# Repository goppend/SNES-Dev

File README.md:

# SNES-Dev
Repo for my Super NES development projects

## SNES-Cart-Dbg
### SNES cartridge debugging probe. With lock-on technology!

## SNES-Cart-Holder
### PCB intermediary for plugging SNES cartridges into things.

## SNES-EEPROM
### Small board for adapting PLCC EEPROMs to SNES mask ROMs.

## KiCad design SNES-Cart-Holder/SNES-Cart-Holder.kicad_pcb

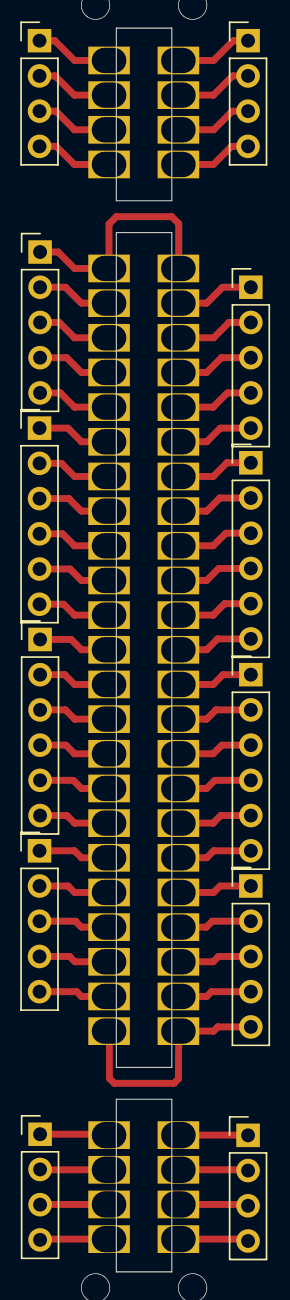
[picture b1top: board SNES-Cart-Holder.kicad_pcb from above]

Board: 2 copper layers, 13 parts (0 on the bottom side), 60 nets.

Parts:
J1, J6, J8, J13: Conn_01x04_Male; PinHeader_1x04_P2.54mm_Vertical
J2, J5, J9, J12: Conn_01x05_Male; PinHeader_1x05_P2.54mm_Vertical
J3, J4, J10, J11: Conn_01x06_Male; PinHeader_1x06_P2.54mm_Vertical
J7: Conn_02x31_Top_Bottom; SNES_Cart_Holder_Pogo

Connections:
/#CPURD: J5.2, J7.23
/#CPUWR: J7.54, J12.1
/#IRQ: J4.3, J7.18
/#PARD: J1.4, J7.4
/#PAWR: J7.35, J8.4
/#RAMSEL: J7.32, J8.1
/#RESET: J5.5, J7.26
/#ROMSEL: J7.49, J11.2
/+5V: J7.27, J7.58, J12.5
/CA0: J4.2, J7.17
/CA1: J4.1, J7.16
/CA2: J3.6, J7.15
/CA3: J3.5, J7.14
/CA4: J3.4, J7.13
/CA5: J3.3, J7.12
/CA6: J3.2, J7.11
/CA7: J3.1, J7.10
/CA8: J2.5, J7.9
/CA9: J2.4, J7.8
/CA10: J2.3, J7.7
/CA11: J2.2, J7.6
/CA12: J7.37, J9.1
/CA13: J7.38, J9.2
/CA14: J7.39, J9.3
/CA15: J7.40, J9.4
/CA16: J7.41, J9.5
/CA17: J7.42, J10.1
/CA18: J7.43, J10.2
/CA19: J7.44, J10.3
/CA20: J7.45, J10.4
/CA21: J7.46, J10.5
/CA22: J7.47, J10.6
/CA23: J7.48, J11.1
/CIC0: J5.3, J7.24
/CIC1: J7.55, J12.2
/CIC2: J5.4, J7.25
/CIC3: J7.56, J12.3
/D0: J4.4, J7.19
/D1: J4.5, J7.20
/D2: J4.6, J7.21
/D3: J5.1, J7.22
/D4: J7.50, J11.3
/D5: J7.51, J11.4
/D6: J7.52, J11.5
/D7: J7.53, J11.6
/EXPAND: J1.2, J7.2
/GND: J2.1, J7.5, J7.36
/MCK: J1.1, J7.1
/PA0: J6.1, J7.28
/PA1: J7.59, J13.1
/PA2: J6.2, J7.29
/PA3: J7.60, J13.2
/PA4: J6.3, J7.30
/PA5: J7.61, J13.3
/PA6: J1.3, J7.3
/PA7: J7.34, J8.3
/REFRESH: J7.33, J8.2
/SOUND_L: J6.4, J7.31
/SOUND_R: J7.62, J13.4
/SYSCK: J7.57, J12.4

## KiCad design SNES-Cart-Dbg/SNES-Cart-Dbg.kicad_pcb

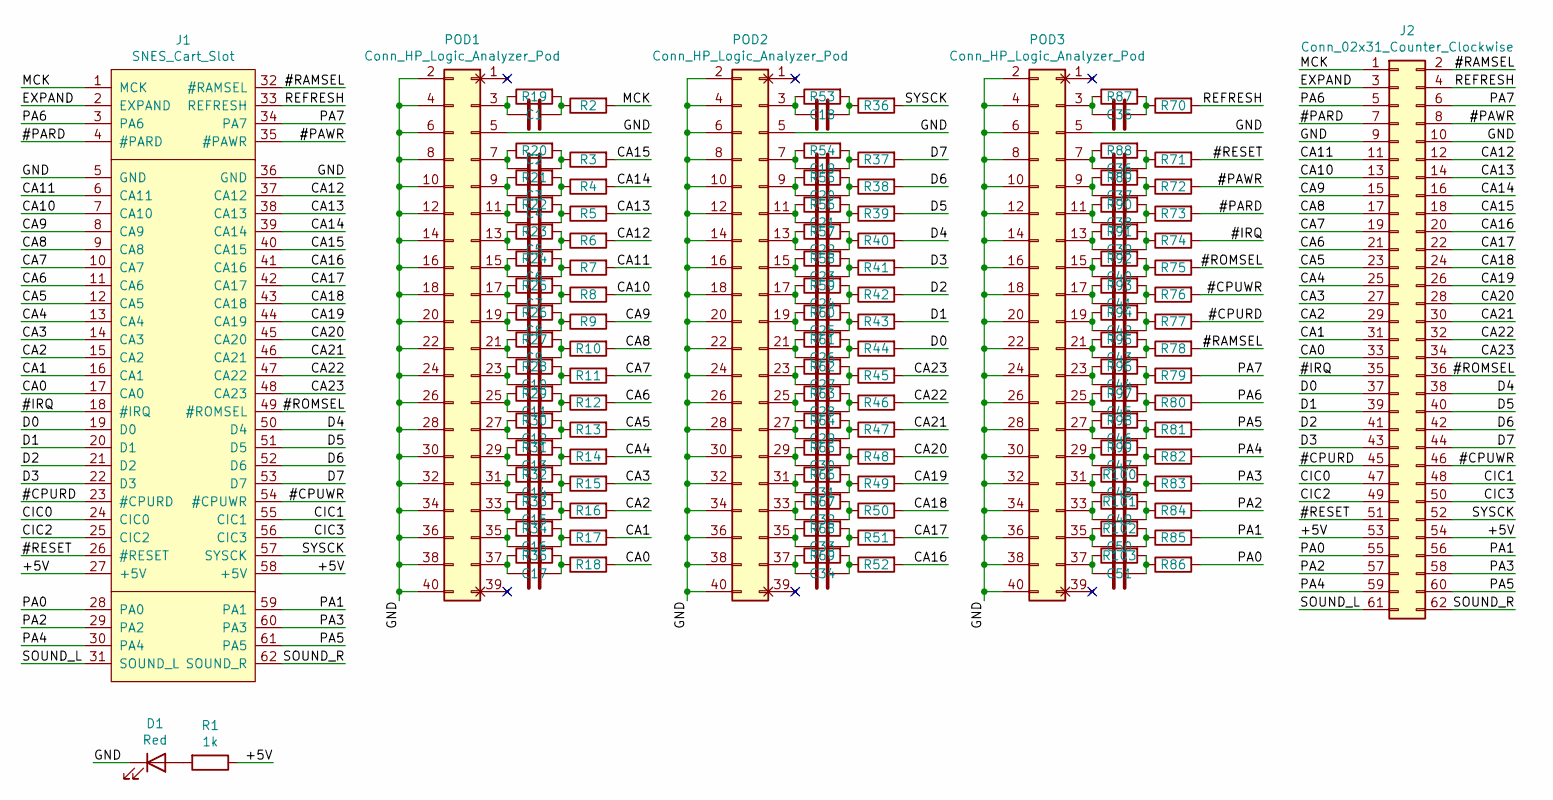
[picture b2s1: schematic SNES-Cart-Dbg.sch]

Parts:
C1: 8 pF; R_0805
C2, C3, C4, C5, C6, C7, C8, C9, C10, C11, C12, C13, C14, C15, C16, C17, C18, C19, C20, C21, C22, C23, C24, C25, C26, C27, C28, C29, C30, C31, C32, C33, C34, C35, C36, C37, C38, C39, C40, C41, C42, C43, C44, C45, C46, C47, C48, C49, C50, C51: C; R_0805
D1: Red; LED_D5.0mm
J1: SNES_Cart_Slot; SNES-Cart
J2: Conn_02x31_Counter_Clockwise; SNES_Connector_Right_Angle
POD1, POD2, POD3: Conn_HP_Logic_Analyzer_Pod; HP_Logic_Analyzer_Pod_Connector
R1: 1k; R_Axial_DIN0204_L3.6mm_D1.6mm_P7.62mm_Horizontal
R2: 250; R_0805
R3, R4, R5, R6, R7, R8, R9, R10, R11, R12, R13, R14, R15, R16, R17, R18, R20, R21, R22, R23, R24, R25, R26, R27, R28, R29, R30, R31, R32, R33, R34, R35, R36, R37, R38, R39, R40, R41, R42, R43, R44, R45, R46, R47, R48, R49, R50, R51, R52, R53, R54, R55, R56, R57, R58, R59, R60, R61, R62, R63, R64, R65, R66, R67, R68, R69, R70, R71, R72, R73, R74, R75, R76, R77, R78, R79, R80, R81, R82, R83, R84, R85, R86, R87, R88, R89, R90, R91, R92, R93, R94, R95, R96, R97, R98, R99, R100, R101, R102, R103: R; R_0805
R19: 10k; R_0805

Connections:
/#CPURD: J1.23 (#CPURD), J2.45, R77.2
/#CPUWR: J1.54 (#CPUWR), J2.46, R76.2
/#IRQ: J1.18 (#IRQ), J2.35, R74.2
/#PARD: J1.4 (#PARD), J2.7, R73.2
/#PAWR: J1.35 (#PAWR), J2.8, R72.2
/#RAMSEL: J1.32 (#RAMSEL), J2.2, R78.2
/#RESET: J1.26 (#RESET), J2.51, R71.2
/#ROMSEL: J1.49 (#ROMSEL), J2.36, R75.2
/+5V: J1.27 (+5V), J1.58 (+5V), J2.53, J2.54, R1.1
/CA0: J1.17 (CA0), J2.33, R18.2
/CA1: J1.16 (CA1), J2.31, R17.2
/CA2: J1.15 (CA2), J2.29, R16.2
/CA3: J1.14 (CA3), J2.27, R15.2
/CA4: J1.13 (CA4), J2.25, R14.2
/CA5: J1.12 (CA5), J2.23, R13.2
/CA6: J1.11 (CA6), J2.21, R12.2
/CA7: J1.10 (CA7), J2.19, R11.2
/CA8: J1.9 (CA8), J2.17, R10.2
/CA9: J1.8 (CA9), J2.15, R9.2
/CA10: J1.7 (CA10), J2.13, R8.2
/CA11: J1.6 (CA11), J2.11, R7.2
/CA12: J1.37 (CA12), J2.12, R6.2
/CA13: J1.38 (CA13), J2.14, R5.2
/CA14: J1.39 (CA14), J2.16, R4.2
/CA15: J1.40 (CA15), J2.18, R3.2
/CA16: J1.41 (CA16), J2.20, R52.2
/CA17: J1.42 (CA17), J2.22, R51.2
/CA18: J1.43 (CA18), J2.24, R50.2
/CA19: J1.44 (CA19), J2.26, R49.2
/CA20: J1.45 (CA20), J2.28, R48.2
/CA21: J1.46 (CA21), J2.30, R47.2
/CA22: J1.47 (CA22), J2.32, R46.2
/CA23: J1.48 (CA23), J2.34, R45.2
/CIC0: J1.24 (CIC0), J2.47
/CIC1: J1.55 (CIC1), J2.48
/CIC2: J1.25 (CIC2), J2.49
/CIC3: J1.56 (CIC3), J2.50
/D0: J1.19 (D0), J2.37, R44.2
/D1: J1.20 (D1), J2.39, R43.2
/D2: J1.21 (D2), J2.41, R42.2
/D3: J1.22 (D3), J2.43, R41.2
/D4: J1.50 (D4), J2.38, R40.2
/D5: J1.51 (D5), J2.40, R39.2
/D6: J1.52 (D6), J2.42, R38.2
/D7: J1.53 (D7), J2.44, R37.2
/EXPAND: J1.2 (EXPAND), J2.3
/GND: D1.1 (K), J1.5 (GND), J1.36 (GND), J2.9, J2.10, POD1.2 (Gnd), POD1.4 (Gnd), POD1.5 (Sig_Ref), POD1.6 (Gnd), POD1.8 (Gnd), POD1.10 (Gnd), POD1.12 (Gnd), POD1.14 (Gnd), POD1.16 (Gnd), POD1.18 (Gnd), POD1.20 (Gnd), POD1.22 (Gnd), POD1.24 (Gnd), POD1.26 (Gnd), POD1.28 (Gnd), POD1.30 (Gnd), POD1.32 (Gnd), POD1.34 (Gnd), POD1.36 (Gnd), POD1.38 (Gnd), POD1.40 (Gnd), POD2.2 (Gnd), POD2.4 (Gnd), POD2.5 (Sig_Ref), POD2.6 (Gnd), POD2.8 (Gnd), POD2.10 (Gnd), POD2.12 (Gnd), POD2.14 (Gnd), POD2.16 (Gnd), POD2.18 (Gnd), POD2.20 (Gnd), POD2.22 (Gnd), POD2.24 (Gnd), POD2.26 (Gnd), POD2.28 (Gnd), POD2.30 (Gnd), POD2.32 (Gnd), POD2.34 (Gnd), POD2.36 (Gnd), POD2.38 (Gnd), POD2.40 (Gnd), POD3.2 (Gnd), POD3.4 (Gnd), POD3.5 (Sig_Ref), POD3.6 (Gnd), POD3.8 (Gnd), POD3.10 (Gnd), POD3.12 (Gnd), POD3.14 (Gnd), POD3.16 (Gnd), POD3.18 (Gnd), POD3.20 (Gnd), POD3.22 (Gnd), POD3.24 (Gnd), POD3.26 (Gnd), POD3.28 (Gnd), POD3.30 (Gnd), POD3.32 (Gnd), POD3.34 (Gnd), POD3.36 (Gnd), POD3.38 (Gnd), POD3.40 (Gnd)
/MCK: J1.1 (MCK), J2.1, R2.2
/REFRESH: J1.33 (REFRESH), J2.4, R70.2
/SOUND_L: J1.31 (SOUND_L), J2.61
/SOUND_R: J1.62 (SOUND_R), J2.62
/SYSCK: J1.57 (SYSCK), J2.52, R36.2
unnamed: C1.1, POD1.3 (Clk), R19.1
unnamed: C1.2, R2.1, R19.2
unnamed: C2.1, POD1.7 (Sig_15), R20.1
unnamed: C2.2, R3.1, R20.2
unnamed: C3.1, POD1.9 (Sig_14), R21.1
unnamed: C3.2, R4.1, R21.2
unnamed: C4.1, POD1.11 (Sig_13), R22.1
unnamed: C4.2, R5.1, R22.2
unnamed: C5.1, POD1.13 (Sig_12), R23.1
unnamed: C5.2, R6.1, R23.2
unnamed: C6.1, POD1.15 (Sig_11), R24.1
unnamed: C6.2, R7.1, R24.2
unnamed: C7.1, POD1.17 (Sig_10), R25.1
unnamed: C7.2, R8.1, R25.2
unnamed: C8.1, POD1.19 (Sig_9), R26.1
unnamed: C8.2, R9.1, R26.2
unnamed: C9.1, POD1.21 (Sig_8), R27.1
unnamed: C9.2, R10.1, R27.2
unnamed: C10.1, POD1.23 (Sig_7), R28.1
unnamed: C10.2, R11.1, R28.2
unnamed: C11.1, POD1.25 (Sig_6), R29.1
unnamed: C11.2, R12.1, R29.2
unnamed: C12.1, POD1.27 (Sig_5), R30.1
unnamed: C12.2, R13.1, R30.2
unnamed: C13.1, POD1.29 (Sig_4), R31.1
unnamed: C13.2, R14.1, R31.2
unnamed: C14.1, POD1.31 (Sig_3), R32.1
unnamed: C14.2, R15.1, R32.2
unnamed: C15.1, POD1.33 (Sig_2), R33.1
unnamed: C15.2, R16.1, R33.2
unnamed: C16.1, POD1.35 (Sig_1), R34.1
unnamed: C16.2, R17.1, R34.2
unnamed: C17.1, POD1.37 (Sig_0), R35.1
unnamed: C17.2, R18.1, R35.2
unnamed: C18.1, POD2.3 (Clk), R53.1
unnamed: C18.2, R36.1, R53.2
unnamed: C19.1, POD2.7 (Sig_15), R54.1
unnamed: C19.2, R37.1, R54.2
unnamed: C20.1, POD2.9 (Sig_14), R55.1
unnamed: C20.2, R38.1, R55.2
unnamed: C21.1, POD2.11 (Sig_13), R56.1
unnamed: C21.2, R39.1, R56.2
unnamed: C22.1, POD2.13 (Sig_12), R57.1
unnamed: C22.2, R40.1, R57.2
unnamed: C23.1, POD2.15 (Sig_11), R58.1
unnamed: C23.2, R41.1, R58.2
unnamed: C24.1, POD2.17 (Sig_10), R59.1
unnamed: C24.2, R42.1, R59.2
unnamed: C25.1, POD2.19 (Sig_9), R60.1
unnamed: C25.2, R43.1, R60.2
unnamed: C26.1, POD2.21 (Sig_8), R61.1
unnamed: C26.2, R44.1, R61.2
unnamed: C27.1, POD2.23 (Sig_7), R62.1
unnamed: C27.2, R45.1, R62.2
unnamed: C28.1, POD2.25 (Sig_6), R63.1
unnamed: C28.2, R46.1, R63.2
unnamed: C29.1, POD2.27 (Sig_5), R64.1
unnamed: C29.2, R47.1, R64.2
unnamed: C30.1, POD2.29 (Sig_4), R65.1
unnamed: C30.2, R48.1, R65.2
unnamed: C31.1, POD2.31 (Sig_3), R66.1
unnamed: C31.2, R49.1, R66.2
unnamed: C32.1, POD2.33 (Sig_2), R67.1
unnamed: C32.2, R50.1, R67.2
unnamed: C33.1, POD2.35 (Sig_1), R68.1
unnamed: C33.2, R51.1, R68.2
unnamed: C34.1, POD2.37 (Sig_0), R69.1
unnamed: C34.2, R52.1, R69.2
unnamed: C35.1, POD3.3 (Clk), R87.1
unnamed: C35.2, R70.1, R87.2
unnamed: C36.1, POD3.7 (Sig_15), R88.1
unnamed: C36.2, R71.1, R88.2
unnamed: C37.1, POD3.9 (Sig_14), R89.1
unnamed: C37.2, R72.1, R89.2
unnamed: C38.1, POD3.11 (Sig_13), R90.1
unnamed: C38.2, R73.1, R90.2
unnamed: C39.1, POD3.13 (Sig_12), R91.1
unnamed: C39.2, R74.1, R91.2
unnamed: C40.1, POD3.15 (Sig_11), R92.1
unnamed: C40.2, R75.1, R92.2
unnamed: C41.1, POD3.17 (Sig_10), R93.1
unnamed: C41.2, R76.1, R93.2
unnamed: C42.1, POD3.19 (Sig_9), R94.1
unnamed: C42.2, R77.1, R94.2
unnamed: C43.1, POD3.21 (Sig_8), R95.1
unnamed: C43.2, R78.1, R95.2
unnamed: C44.1, POD3.23 (Sig_7), R96.1
unnamed: C44.2, R79.1, R96.2
unnamed: C45.1, POD3.25 (Sig_6), R97.1
unnamed: C45.2, R80.1, R97.2
unnamed: C46.1, POD3.27 (Sig_5), R98.1
unnamed: C46.2, R81.1, R98.2
unnamed: C47.1, POD3.29 (Sig_4), R99.1
unnamed: C47.2, R82.1, R99.2
unnamed: C48.1, POD3.31 (Sig_3), R100.1
unnamed: C48.2, R83.1, R100.2
unnamed: C49.1, POD3.33 (Sig_2), R101.1
unnamed: C49.2, R84.1, R101.2
unnamed: C50.1, POD3.35 (Sig_1), R102.1
unnamed: C50.2, R85.1, R102.2
unnamed: C51.1, POD3.37 (Sig_0), R103.1
unnamed: C51.2, R86.1, R103.2
unnamed: D1.2 (A), R1.2

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
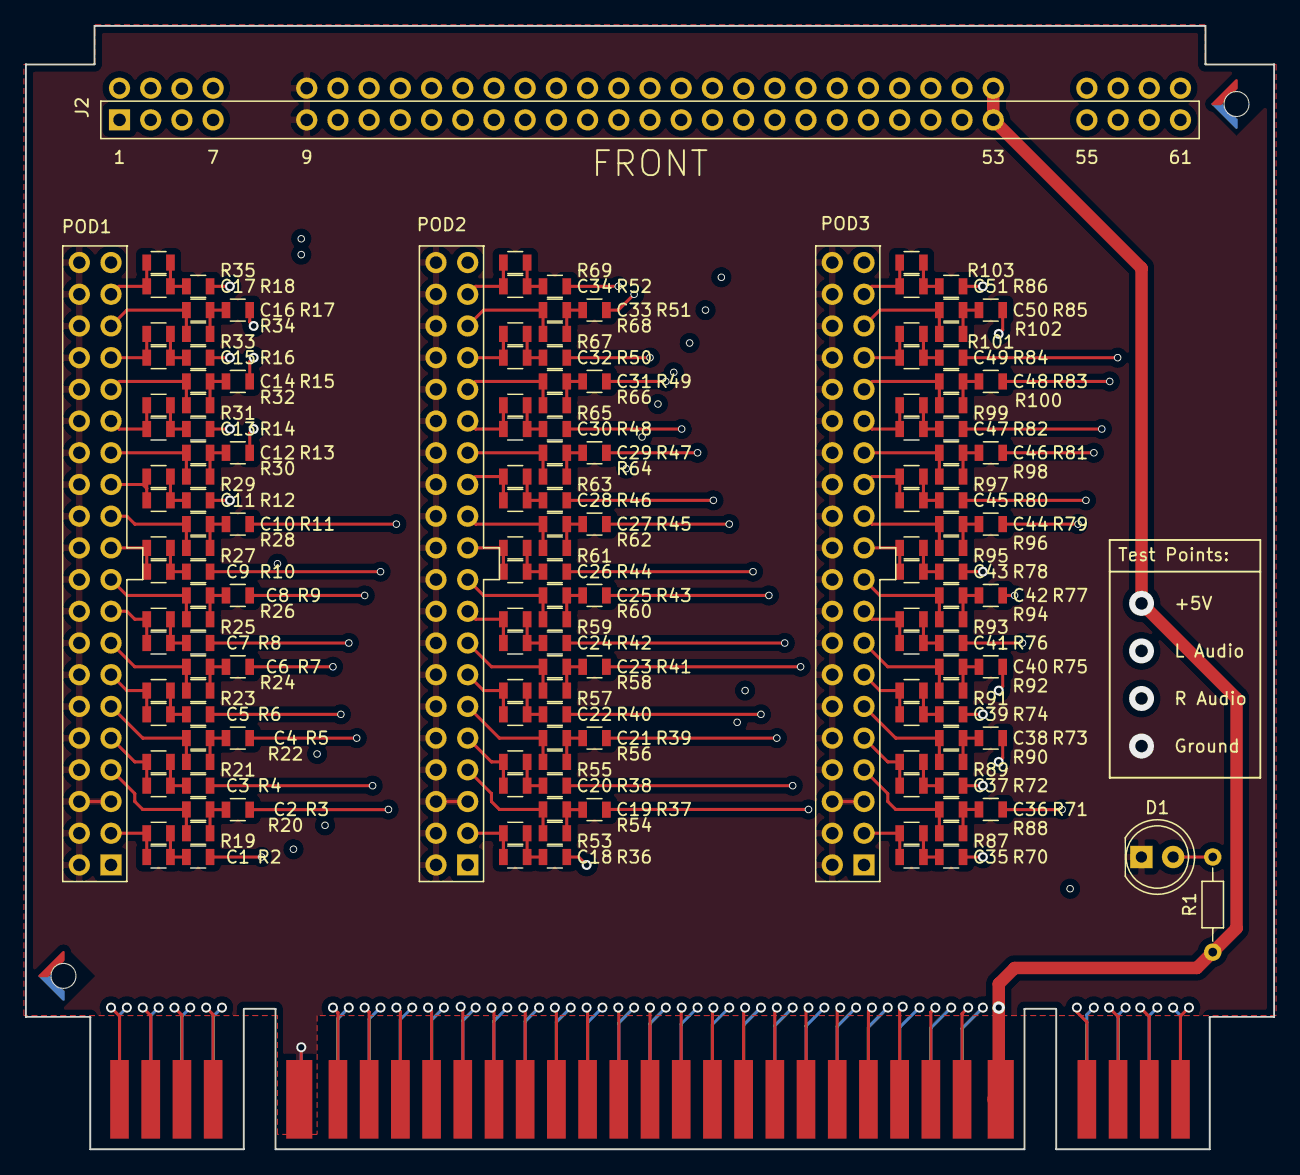
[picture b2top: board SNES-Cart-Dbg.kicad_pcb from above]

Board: 4 copper layers, 100.0 x 90.0 mm, 160 parts (0 on the bottom side), 163 nets.

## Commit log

2022-03-05 Initial commit, with v2 cart debug probe, v2 cart holder, and v1 EEPROM adapter.
